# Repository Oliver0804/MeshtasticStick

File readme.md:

# MeshtasticStick

1. 支持太陽能（0.3V~5.5V）
2. 支持寬壓輸入（4.5V~28V）
3. TypeC 供電(輸入最少5V/1.5A)，如無充電狀況下約0.8A
4. NRF52 不支持WI-FI
5. 預留I2C,GPS接口(GPS可使用Jumper切換電壓3v3/5v0)

# 原理圖

# 主要零件
1. MDBT50Q-P1MV2
描述: 這是由Raytac Corporation生產的一款BLE模塊，基於Nordic Semiconductor的nRF52840晶片。此模塊支持Bluetooth 5.1規範，具有低功耗藍牙(BLE)功能。
優勢: 具有較大的傳輸範圍、高數據傳輸速率和低能耗。支持多種無線通訊協議，包括藍牙、ANT和2.4 GHz射頻。此外，內建32位ARM Cortex-M4 CPU，具有豐富的GPIO和接口，適合複雜的物聯網(IoT)應用。

2. SPV1040（voltage range from 0.3 V to 5.5 V）
描述: SPV1040是STMicroelectronics的一款高效率太陽能充電控制器，適用於低功耗應用和可攜式太陽能系統。
優勢: 能夠在廣泛的太陽照射條件下有效提高能量收集效率，支持最大功率點追蹤(MPPT)技術，以最大化太陽能板的能量輸出。此IC具有過載保護和熱保護功能，能確保系統的穩定與安全。

3. L6924 (取代LT4056系列)
描述: L6924是一款用於單節鋰離子或鋰聚合物電池的充電管理IC，由STMicroelectronics製造。
優勢: 這個充電器支持調整充電電流和電壓，以適應不同電池的需求。它包括內部功率晶體管和電流感測功能，無需外部許多元件，非常適合便攜式設備。

4. MP2338 (4.5V to 28V Operating Input Range)
描述: MP2338是由MPS公司生產的一款同步降壓轉換器，用於將更高的電壓轉換為更低的電壓，同時提供高效率和優異的負載調節。
優勢: 它具有高達95%的轉換效率，非常適合需要高效能轉換的應用。此外，其具有緊湊的尺寸和低靜態功耗，非常適合電池供電的系統。

5. E22-900M30/33 1W LORA
描述: Ebyte製造的E22-900M30/33是一款高功率LoRa模塊，工作在900 MHz頻段，提供長距離無線通信。
優勢: 此模塊的最大發射功率達到1瓦特，能夠實現極遠的通信距離。支持LoRa和FSK調制，具有良好的抗干擾性能和低功耗特性。此外，模塊的配置靈活，支持多種工作模式，非常適合需要遠距離數據傳輸的物聯網應用。

# TODO
- [ ] 確認SPV1040工作狀態
- [ ] L6924 ST1,ST2確認設計方式
- [ ] 確認4.2v供電

# ref

- 太陽能設計文件
https://static5.arrow.com/pdfs/2011/10/8/19/12/15/660/st_/auto/steval-isv012v1_schematic.pdf

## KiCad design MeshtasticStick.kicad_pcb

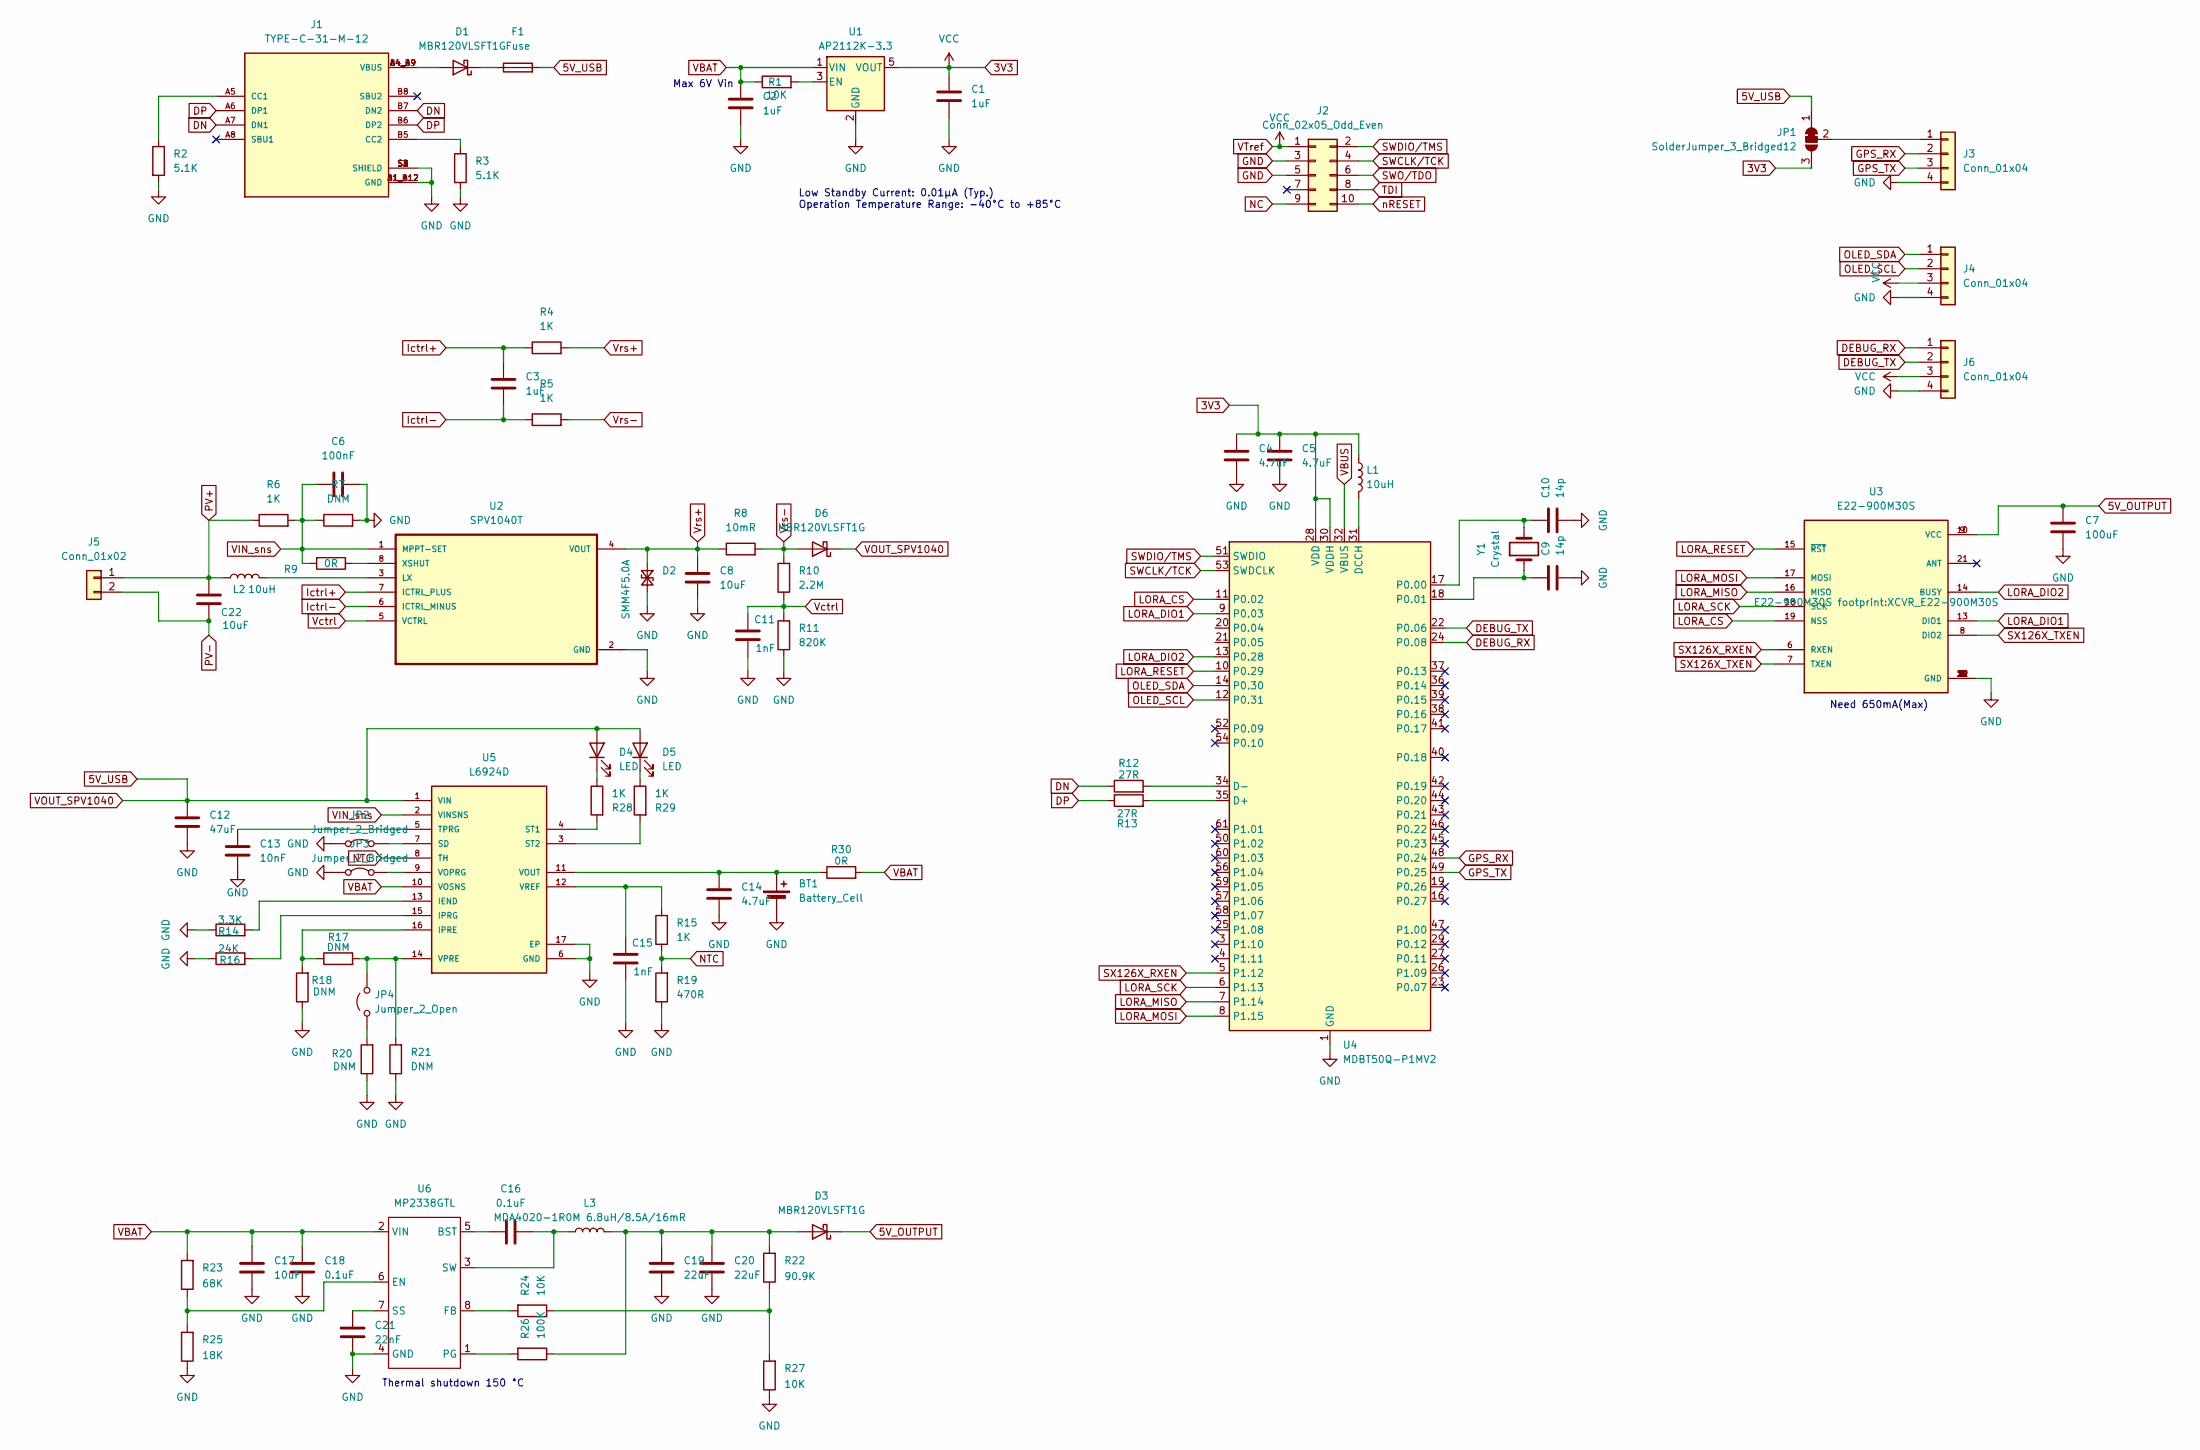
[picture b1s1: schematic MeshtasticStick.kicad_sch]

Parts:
BT1: Battery_Cell; PinHeader_1x02_P2.54mm_Vertical
C1, C2, C3: 1uF; C_0603_1608Metric
C4, C5, C14: 4.7uF; C_0603_1608Metric
C6: 100nF; C_0603_1608Metric
C7: 100uF; CP_Elec_6.3x7.7
C8, C17, C22: 10uF; C_0603_1608Metric
C9, C10: 14p; C_0603_1608Metric
C11, C15: 1nF; C_0603_1608Metric
C12: 47uF; CP_Elec_6.3x7.7
C13: 10nF; C_0603_1608Metric
C16, C18: 0.1uF; C_0603_1608Metric
C19, C20: 22uF; C_0805_2012Metric
C21: 22nF; C_0603_1608Metric
D1, D3, D6: MBR120VLSFT1G; D_SOD-123F
D2: SMM4F5.0A; D_SMP_DO-220AA
D4, D5: LED; LED_0603_1608Metric
F1: Fuse; Fuse_1210_3225Metric
J1: TYPE-C-31-M-12; HRO_TYPE-C-31-M-12; PARTREV 2020.12.08
J2: Conn_02x05_Odd_Even; PinHeader_2x05_P1.27mm_Vertical
J3, J4, J6: Conn_01x04; PinHeader_1x04_P2.54mm_Vertical
J5: Conn_01x02; PinHeader_1x02_P2.54mm_Vertical
JP1: SolderJumper_3_Bridged12; SolderJumper-3_P1.3mm_Open_RoundedPad1.0x1.5mm
JP2, JP3: Jumper_2_Bridged; SolderJumper-2_P1.3mm_Bridged2Bar_RoundedPad1.0x1.5mm
JP4: Jumper_2_Open; SolderJumper-2_P1.3mm_Open_RoundedPad1.0x1.5mm
L1: 10uH; L_1210_3225Metric
L2: 10uH; Fuse_1210_3225Metric
L3: MDA4020-1R0M 6.8uH/8.5A/16mR; L_Coilcraft_XAL6060-XXX
R1, R24, R27: 10K; R_0603_1608Metric
R2, R3: 5.1K; R_0603_1608Metric
R4, R5, R6, R15, R28, R29: 1K; R_0603_1608Metric
R7, R17, R18, R20, R21: DNM; R_0603_1608Metric
R8: 10mR; R_1210_3225Metric
R9, R30: 0R; R_0603_1608Metric
R10: 2.2M; R_0603_1608Metric
R11: 820K; R_0603_1608Metric
R12, R13: 27R; R_0603_1608Metric
R14: 3.3K; R_0603_1608Metric
R16: 24K; R_0603_1608Metric
R19: 470R; R_0603_1608Metric
R22: 90.9K; R_0603_1608Metric
R23: 68K; R_0603_1608Metric
R25: 18K; R_0603_1608Metric
R26: 100K; R_0603_1608Metric
U1: AP2112K-3.3; SOT-23-5
U2: SPV1040T; SOP65P640X120-8N; PARTREV 7
U3: E22-900M30S; XCVR_E22-900M30S; PARTREV 1.2
U4: MDBT50Q-P1MV2; Raytac_MDBT50Q
U5: L6924D; QFN50P300X300X100-17N
U6: MP2338GTL; SOT-583-8
Y1: Crystal; Crystal_SMD_2012-2Pin_2.0x1.2mm

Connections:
3V3: C1.1, C4.1, C5.1, J2.1, J4.3, J6.3, JP1.3 (B), L1.1, U1.5 (VOUT), U4.28 (VDD), U4.30 (VDDH)
5V_OUTPUT: C7.1, D3.1 (K), U3.9 (VCC), U3.10 (VCC)
5V_USB: C12.1, D4.2 (A), D5.2 (A), D6.1 (K), F1.2, JP1.1 (A), U5.1 (VIN)
DEBUG_RX: J6.1, U4.24 (P0.08)
DEBUG_TX: J6.2, U4.22 (P0.06)
DN: J1.A7 (DN1), J1.B7 (DN2), R12.1
DP: J1.A6 (DP1), J1.B6 (DP2), R13.1
GND: BT1.2 (-), C1.2, C2.2, C4.2, C5.2, C6.2, C7.2, C8.2, C9.2, C10.2, C11.2, C12.2, C13.2, C14.2, C15.2, C17.2, C18.2, C19.2, C20.2, C21.2, D2.2 (A2), J1.A1_B12 (GND), J1.B1_A12 (GND), J1.S1 (SHIELD), J1.S2 (SHIELD), J1.S3 (SHIELD), J1.S4 (SHIELD), J2.3, J2.5, J3.4, J4.4, J6.4, JP2.1 (A), JP3.1 (A), R2.2, R3.2, R7.2, R11.1, R14.1, R16.1, R18.1, R19.1, R20.1, R21.1, R25.1, R27.1, U1.2 (GND), U2.2 (GND), U3.1 (GND), U3.2 (GND), U3.3 (GND), U3.4 (GND), U3.5 (GND), U3.11 (GND), U3.12 (GND), U3.20 (GND), U3.22 (GND), U4.1 (GND), U4.2 (GND), U4.15 (GND), U4.33 (GND), U4.55 (GND), U5.6 (GND), U5.17 (EP), U6.4 (GND)
GPS_RX: J3.2, U4.48 (P0.24)
GPS_TX: J3.3, U4.49 (P0.25)
Ictrl+: C3.2, R4.1, U2.7 (ICTRL_PLUS)
Ictrl-: C3.1, R5.1, U2.6 (ICTRL_MINUS)
LORA_CS: U3.19 (NSS), U4.11 (P0.02)
LORA_DIO1: U3.13 (DIO1), U4.9 (P0.03)
LORA_DIO2: U3.14 (BUSY), U4.13 (P0.28)
LORA_MISO: U3.16 (MISO), U4.7 (P1.14)
LORA_MOSI: U3.17 (MOSI), U4.8 (P1.15)
LORA_RESET: U3.15 (~RST), U4.10 (P0.29)
LORA_SCK: U3.18 (SCK), U4.6 (P1.13)
NC: J2.9
NTC: R15.1, R19.2, U5.8 (TH)
unnamed: BT1.1 (+), C14.1, R30.1, U5.11 (VOUT)
unnamed: D1.2 (A), J1.A4_B9 (VBUS), J1.B4_A9 (VBUS)
unnamed: D1.1 (K), F1.1
unnamed: C19.1, C20.1, D3.2 (A), L3.2, R22.2, R26.1
unnamed: D4.1 (K), R28.1
unnamed: D5.1 (K), R29.1
unnamed: J1.A5 (CC1), R2.1
unnamed: J1.B5 (CC2), R3.1
unnamed: J3.1, JP1.2 (C)
unnamed: JP2.2 (B), U5.7 (SD)
unnamed: JP3.2 (B), U5.9 (VOPRG)
unnamed: JP4.1 (A), R20.2
unnamed: JP4.2 (B), R17.2, R21.2, U5.14 (VPRE)
unnamed: R22.1, R24.1, R27.2
unnamed: R1.2, U1.3 (EN)
unnamed: L2.2, U2.3 (LX)
unnamed: R9.1, U2.8 (XSHUT)
unnamed: R13.2, U4.35 (D+)
unnamed: R12.2, U4.34 (D-)
unnamed: L1.2, U4.31 (DCCH)
unnamed: C10.1, U4.17 (P0.00), Y1.2
unnamed: C9.1, U4.18 (P0.01), Y1.1
unnamed: R14.2, U5.13 (IEND)
unnamed: R17.1, R18.2, U5.16 (IPRE)
unnamed: R16.2, U5.15 (IPRG)
unnamed: R28.2, U5.4 (ST1)
unnamed: R29.2, U5.3 (ST2)
unnamed: C13.1, U5.5 (TPRG)
unnamed: C15.1, R15.2, U5.12 (VREF)
unnamed: C16.1, U6.5 (BST)
unnamed: R23.1, R25.2, U6.6 (EN)
unnamed: R24.2, U6.8 (FB)
unnamed: R26.2, U6.1 (PG)
unnamed: C21.1, U6.7 (SS)
unnamed: C16.2, L3.1, U6.3 (SW)
OLED_SCL: J4.2, U4.12 (P0.31)
OLED_SDA: J4.1, U4.14 (P0.30)
PV+: C22.1, J5.1, L2.1, R6.1
PV-: C22.2, J5.2
SWCLK/TCK: J2.4, U4.53 (SWDCLK)
SWDIO/TMS: J2.2, U4.51 (SWDIO)
SWO/TDO: J2.6
SX126X_RXEN: U3.6 (RXEN), U4.5 (P1.12)
SX126X_TXEN: U3.7 (TXEN), U3.8 (DIO2)
TDI: J2.8
VBAT: C2.1, C17.1, C18.1, R1.1, R23.2, R30.2, U1.1 (VIN), U5.10 (VOSNS), U6.2 (VIN)
VBUS: U4.32 (VBUS)
VIN_sns: C6.1, R6.2, R7.1, R9.2, U2.1 (MPPT-SET), U5.2 (VINSNS)
Vctrl: C11.1, R10.1, R11.2, U2.5 (VCTRL)
Vrs+: C8.1, D2.1 (A1), R4.2, R8.1, U2.4 (VOUT)
Vrs-: D6.2 (A), R5.2, R8.2, R10.2
nRESET: J2.10

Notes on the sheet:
Need 650mA(Max)
Thermal shutdown 150 °C
Max 6V Vin
Low Standby Current: 0.01µA (Typ.) Operation Temperature Range: -40°C to +85°C

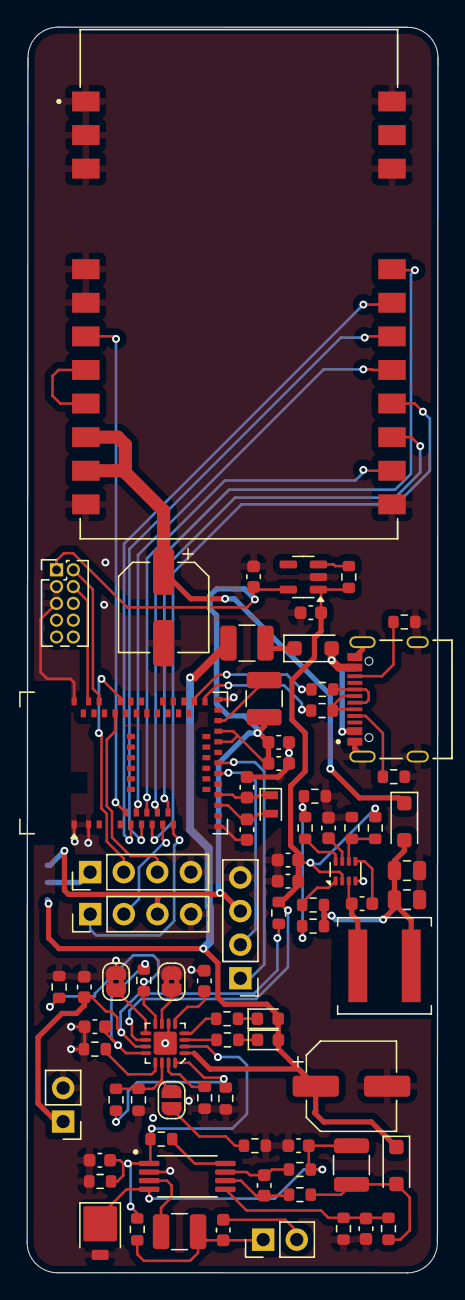
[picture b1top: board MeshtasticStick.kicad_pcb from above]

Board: 2 copper layers, 31.1 x 94.2 mm, 80 parts (1 on the bottom side), 68 nets.

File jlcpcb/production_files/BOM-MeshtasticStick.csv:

Comment,Designator,Footprint,LCSC,Quantity
68K,R23,R_0603_1608Metric,C12036,1
0.1uF,"C16,C18,C6",C_0603_1608Metric,C14663,3
1uF,"C1,C2,C3",C_0603_1608Metric,C15849,3
1nF,"C11,C15",C_0603_1608Metric,C1588,2
100K,R26,R_0603_1608Metric,C17900,1
4.7uF,"C14,C4,C5",C_0603_1608Metric,C19666,3
10uF,"C17,C22,C8",C_0603_1608Metric,C19702,3
SMM4F5.0A,D2,D_SMP_DO-220AA,C1976670,1
Fuse,F1,Fuse_1210_3225Metric,C20806,1
22nF,C21,C_0603_1608Metric,C21122,1
0R,"R30,R9",R_0603_1608Metric,C21189,2
1K,"R15,R28,R29,R4,R5,R6",R_0603_1608Metric,C21190,6
MBR120VLSFT1G,"D1,D3,D6",D_SOD-123F,C223608,3
LED,"D4,D5",LED_0603_1608Metric,C2286,2
2.2M,R10,R_0603_1608Metric,C22938,1
3.3K,R14,R_0603_1608Metric,C22978,1
90.9K,R22,R_0603_1608Metric,C23129,1
470R,R19,R_0603_1608Metric,C23179,1
5.1K,"R2,R3",R_0603_1608Metric,C23186,2
820K,R11,R_0603_1608Metric,C23252,1
24K,R16,R_0603_1608Metric,C23352,1
27R,"R12,R13",R_0603_1608Metric,C25190,2
10K,"R1,R24,R27",R_0603_1608Metric,C25804,3
18K,R25,R_0603_1608Metric,C25810,1
AP2112K-3.3,U1,SOT-23-5,C3021085,1
100uF,C7,CP_Elec_6.3x7.7,C3338,1
47uF,C12,CP_Elec_6.3x7.7,C3344,1
14p,"C10,C9",C_0603_1608Metric,C38523,2
22uF,"C19,C20",C_0805_2012Metric,C45783,2
10nF,C13,C_0603_1608Metric,C57112,1
MP2338GTL,U6,SOT-583-8,C7210174,1
10uH,"L1,L2",L_1210_3225Metric,C86073,2
Crystal,Y1,Crystal_SMD_2012-2Pin_2.0x1.2mm,C90943,1
TYPE-C-31-M-12,J1,HRO_TYPE-C-31-M-12,,1
DNM,R20,R_0603_1608Metric,,1
MDA4020-1R0M  6.8uH/8.5A/16mR,L3,L_Coilcraft_XAL6060-XXX,,1
10mR,R8,R_1210_3225Metric,,1
Conn_01x04,J4,PinHeader_1x04_P2.54mm_Vertical,,1
Conn_02x05_Odd_Even,J2,PinHeader_2x05_P1.27mm_Vertical,,1
DNM,R18,R_0603_1608Metric,,1
DNM,R21,R_0603_1608Metric,,1
L6924D,U5,QFN50P300X300X100-17N,,1
E22-900M30S,U3,XCVR_E22-900M30S,,1
DNM,R17,R_0603_1608Metric,,1
Conn_01x04,J3,PinHeader_1x04_P2.54mm_Vertical,,1
SPV1040T,U2,SOP65P640X120-8N,,1
Jumper_2_Bridged,JP2,SolderJumper-2_P1.3mm_Bridged2Bar_RoundedPad1.0x1.5mm,,1
Conn_01x04,J6,PinHeader_1x04_P2.54mm_Vertical,,1
Jumper_2_Bridged,JP3,SolderJumper-2_P1.3mm_Bridged2Bar_RoundedPad1.0x1.5mm,,1
Conn_01x02,J5,PinHeader_1x02_P2.54mm_Vertical,,1
MDBT50Q-P1MV2,U4,Raytac_MDBT50Q,,1
Battery_Cell,BT1,PinHeader_1x02_P2.54mm_Vertical,,1
Jumper_2_Open,JP4,SolderJumper-2_P1.3mm_Open_RoundedPad1.0x1.5mm,,1
DNM,R7,R_0603_1608Metric,,1

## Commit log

2024-08-11 ver1
2024-11-02 [fix] Fix power supply issue and capacitor packaging, complete initial routing
    - Fixed power supply issue to improve stability
    - Adjusted certain capacitor packages to meet design requirements
    - Completed initial PCB routing
    - Corrected OLED signal routing to ensure proper display
2024-11-15 添加貼片完成照片
